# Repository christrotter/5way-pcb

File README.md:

# 5way-pcb
Simple breakout for a 5-way switch - or is it???  (yes, it is)

20240129 - update, got 10 of these through JLCPCB and they work just fine.  The SKRHACE010 is quite small compared to what I have used in the past, but works great.

# features
- takes a simple 5-way switch and makes it mountable.
 - Mk17 used cheapie 5-ways and the play they have is terrible.
 - I made another breakout for an RKJXT but it requires quite a lot of force to actuate.
 - The Alps SKRHACE010 has low force and low play - but is SMD, so I had to get it assembled.
 - https://www.alps.com/prod/info/E/HTML/MultiControl/Switch/SKRH/SKRHACE010.html
- pigtail pins

Very simple design, meant to nestle into a tight spot.

# schematic

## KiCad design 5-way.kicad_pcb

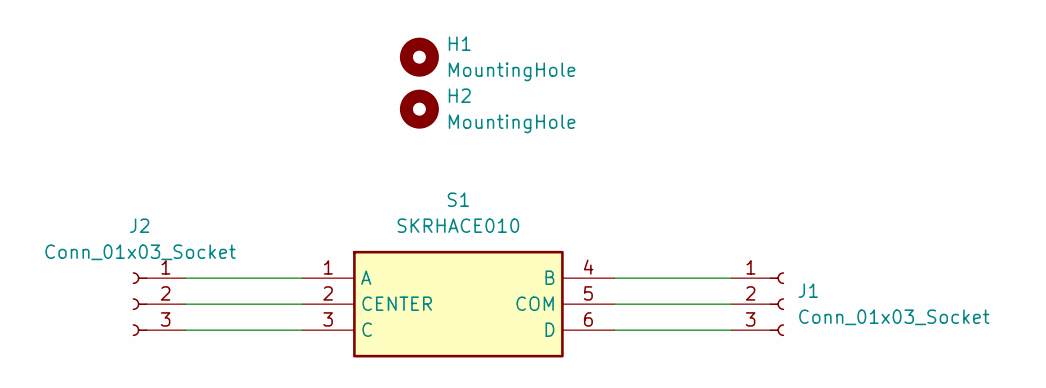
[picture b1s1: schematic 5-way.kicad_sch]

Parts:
H1, H2: MountingHole; MountingHole_3.2mm_M3
J1, J2: Conn_01x03_Socket; PinHeader_1x03_P2.54mm_Vertical
S1: SKRHACE010; SKRHAAE010; Manufacturer_Part_Number SKRHACE010; Mouser Part Number 688-SKRHAC

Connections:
unnamed: J1.1, S1.4 (B)
unnamed: J1.2, S1.5 (COM)
unnamed: J1.3, S1.6 (D)
unnamed: J2.1, S1.1 (A)
unnamed: J2.2, S1.2 (CENTER)
unnamed: J2.3, S1.3 (C)

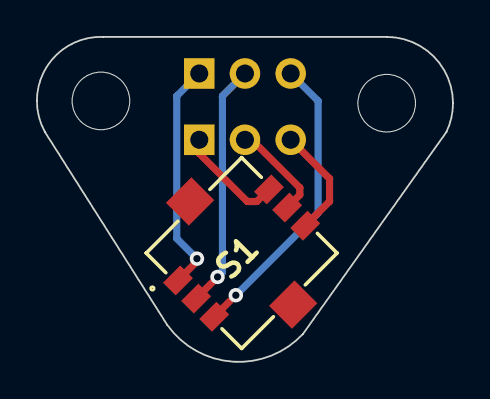
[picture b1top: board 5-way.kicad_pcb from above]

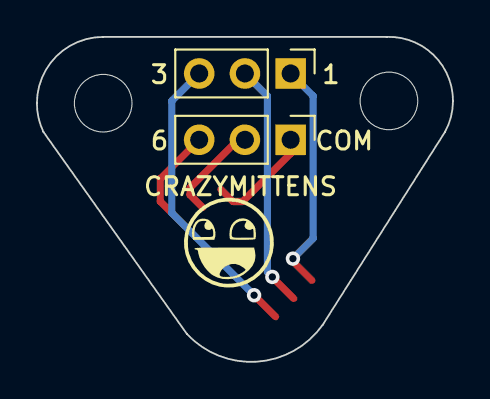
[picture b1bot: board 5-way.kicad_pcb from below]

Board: 2 copper layers, 23.1 x 18.1 mm, 5 parts (2 on the bottom side), 6 nets.

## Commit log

2024-01-07 production pcbs
2024-01-07 adding a readme and doof
